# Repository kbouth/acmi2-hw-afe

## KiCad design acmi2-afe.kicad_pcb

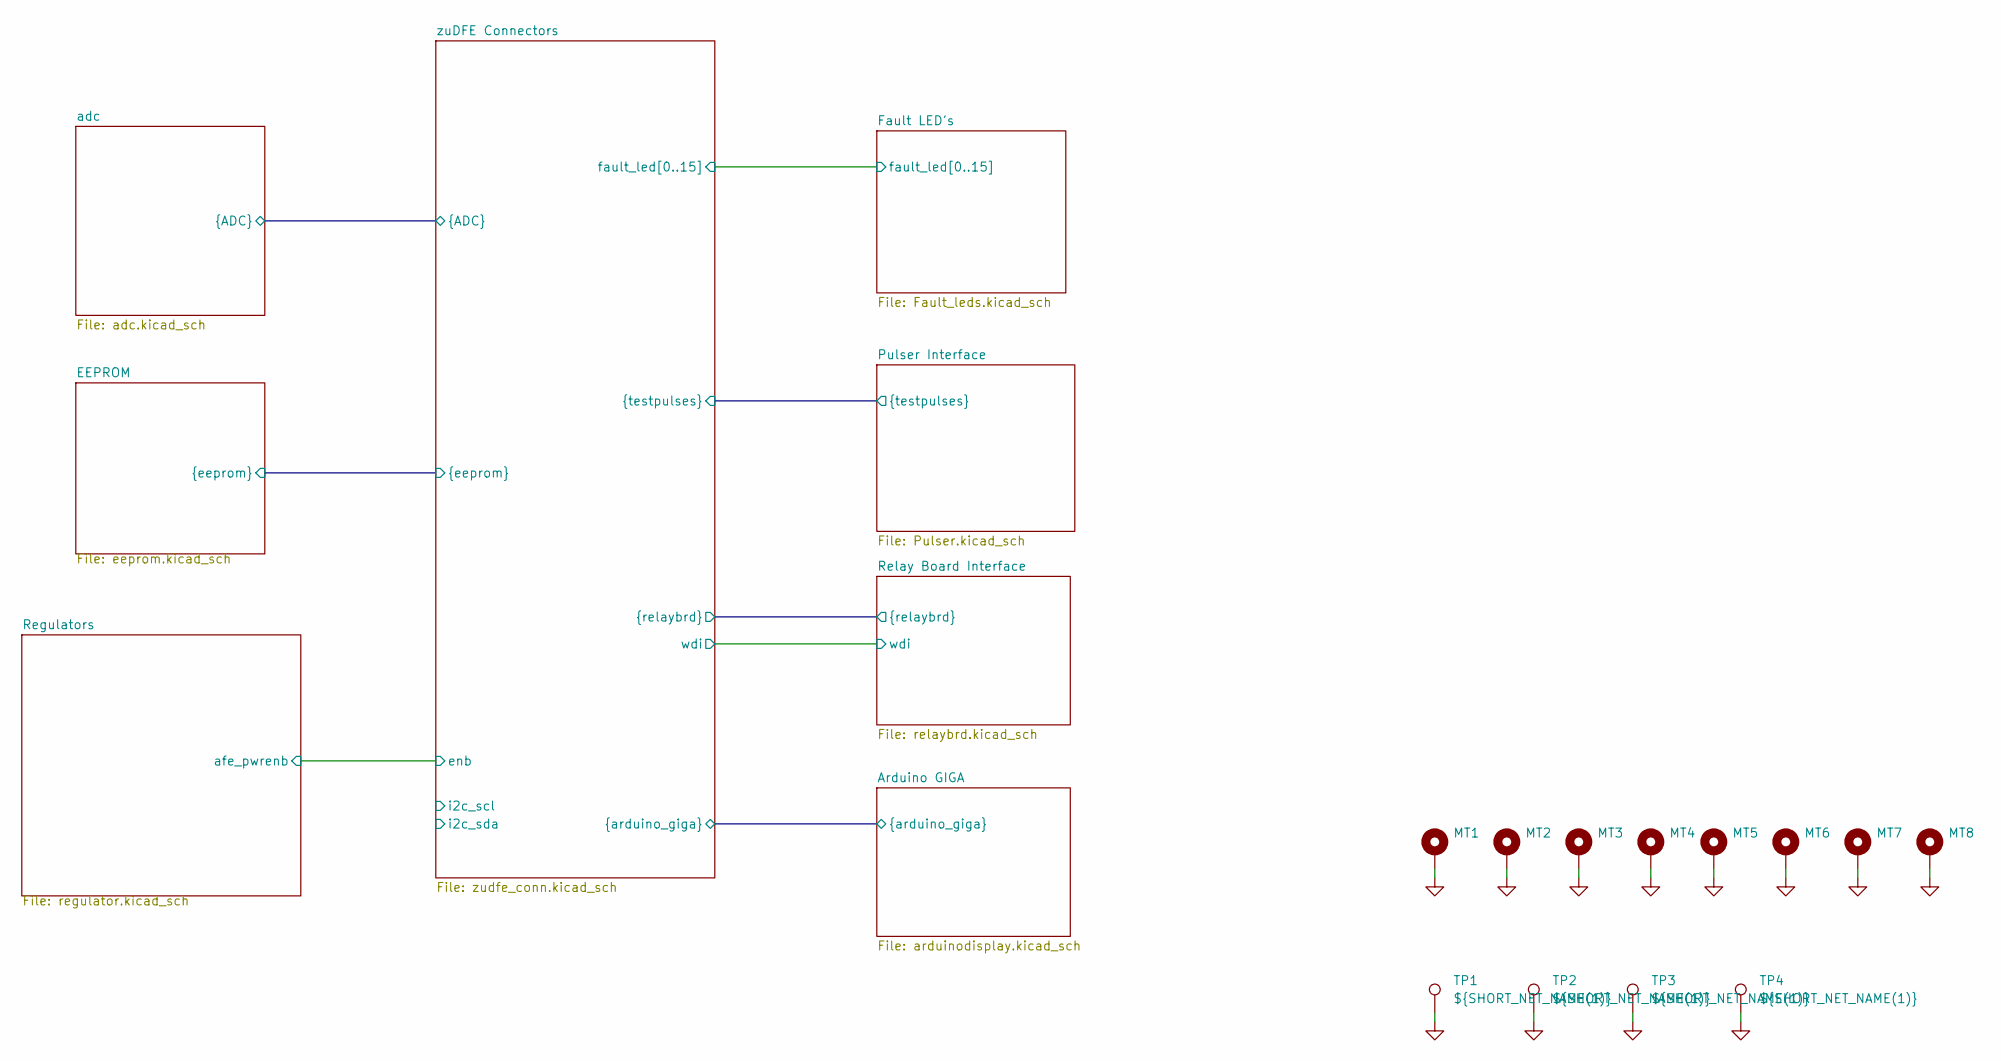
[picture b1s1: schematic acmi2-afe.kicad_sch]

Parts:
MT1, MT2, MT3, MT4, MT5, MT6, MT7, MT8: MountingHole_Pad; MountingHole_4.3mm_M4_DIN965_Pad
TP1, TP2, TP3, TP4: ${SHORT_NET_NAME(1)}; TestPoint_RCS-0C; MFG_PN RCS-0C

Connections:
GND: MT1.1 (1_1), MT2.1 (1_1), MT3.1 (1_1), MT4.1 (1_1), MT5.1 (1_1), MT6.1 (1_1), MT7.1 (1_1), MT8.1 (1_1), TP1.1 (1_1), TP2.1 (1_1), TP3.1 (1_1), TP4.1 (1_1); also elsewhere on the board

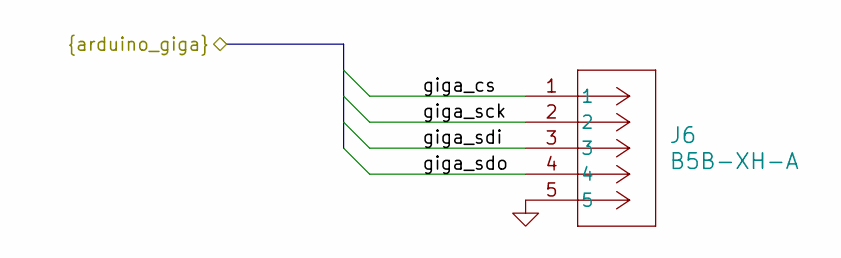
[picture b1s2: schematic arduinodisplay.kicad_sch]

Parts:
J6: B5B-XH-A; CONN_B5B-XH-A_JST

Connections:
/Arduino GIGA/giga_cs: J6.1; also elsewhere on the board
/Arduino GIGA/giga_sck: J6.2; also elsewhere on the board
/Arduino GIGA/giga_sdi: J6.3; also elsewhere on the board
/Arduino GIGA/giga_sdo: J6.4; also elsewhere on the board
GND: J6.5; also elsewhere on the board

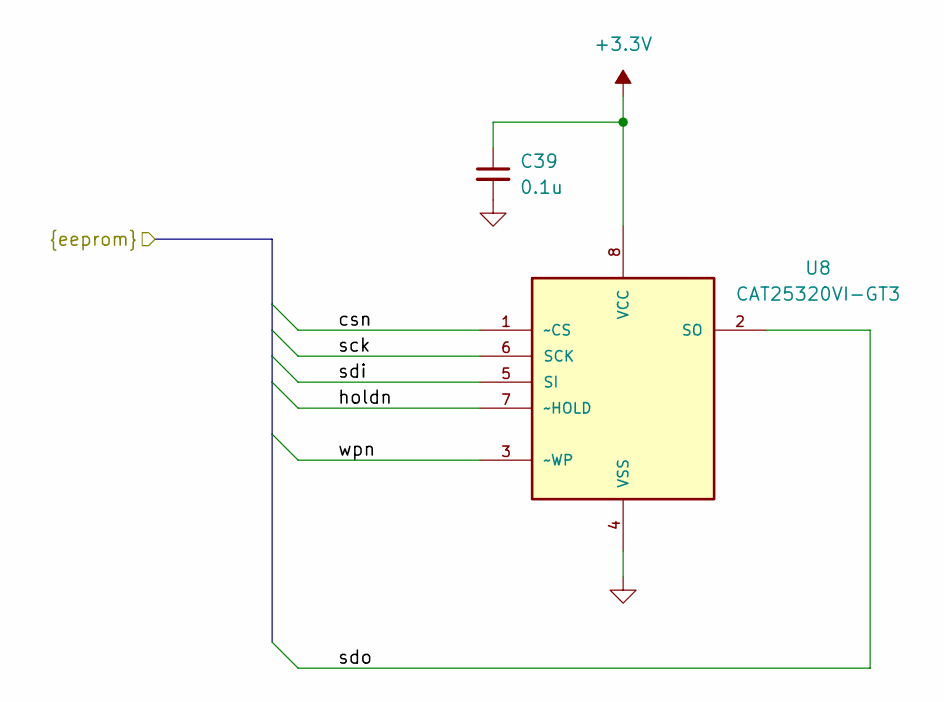
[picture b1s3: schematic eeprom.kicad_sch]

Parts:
C39: 0.1u; C_0805_2012Metric; MFG_PN TMF212B7104KGHT
U8: CAT25320VI-GT3; SOIC127P600X175-8N; MFG_PN CAT25320VI-GT3

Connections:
+3.3V: C39.1, U8.8 (VCC); also elsewhere on the board
/EEPROM/csn: U8.1 (~CS); also elsewhere on the board
/EEPROM/holdn: U8.7 (~HOLD); also elsewhere on the board
/EEPROM/sck: U8.6 (SCK); also elsewhere on the board
/EEPROM/sdi: U8.5 (SI); also elsewhere on the board
/EEPROM/sdo: U8.2 (SO); also elsewhere on the board
/EEPROM/wpn: U8.3 (~WP); also elsewhere on the board
GND: C39.2, U8.4 (VSS); also elsewhere on the board

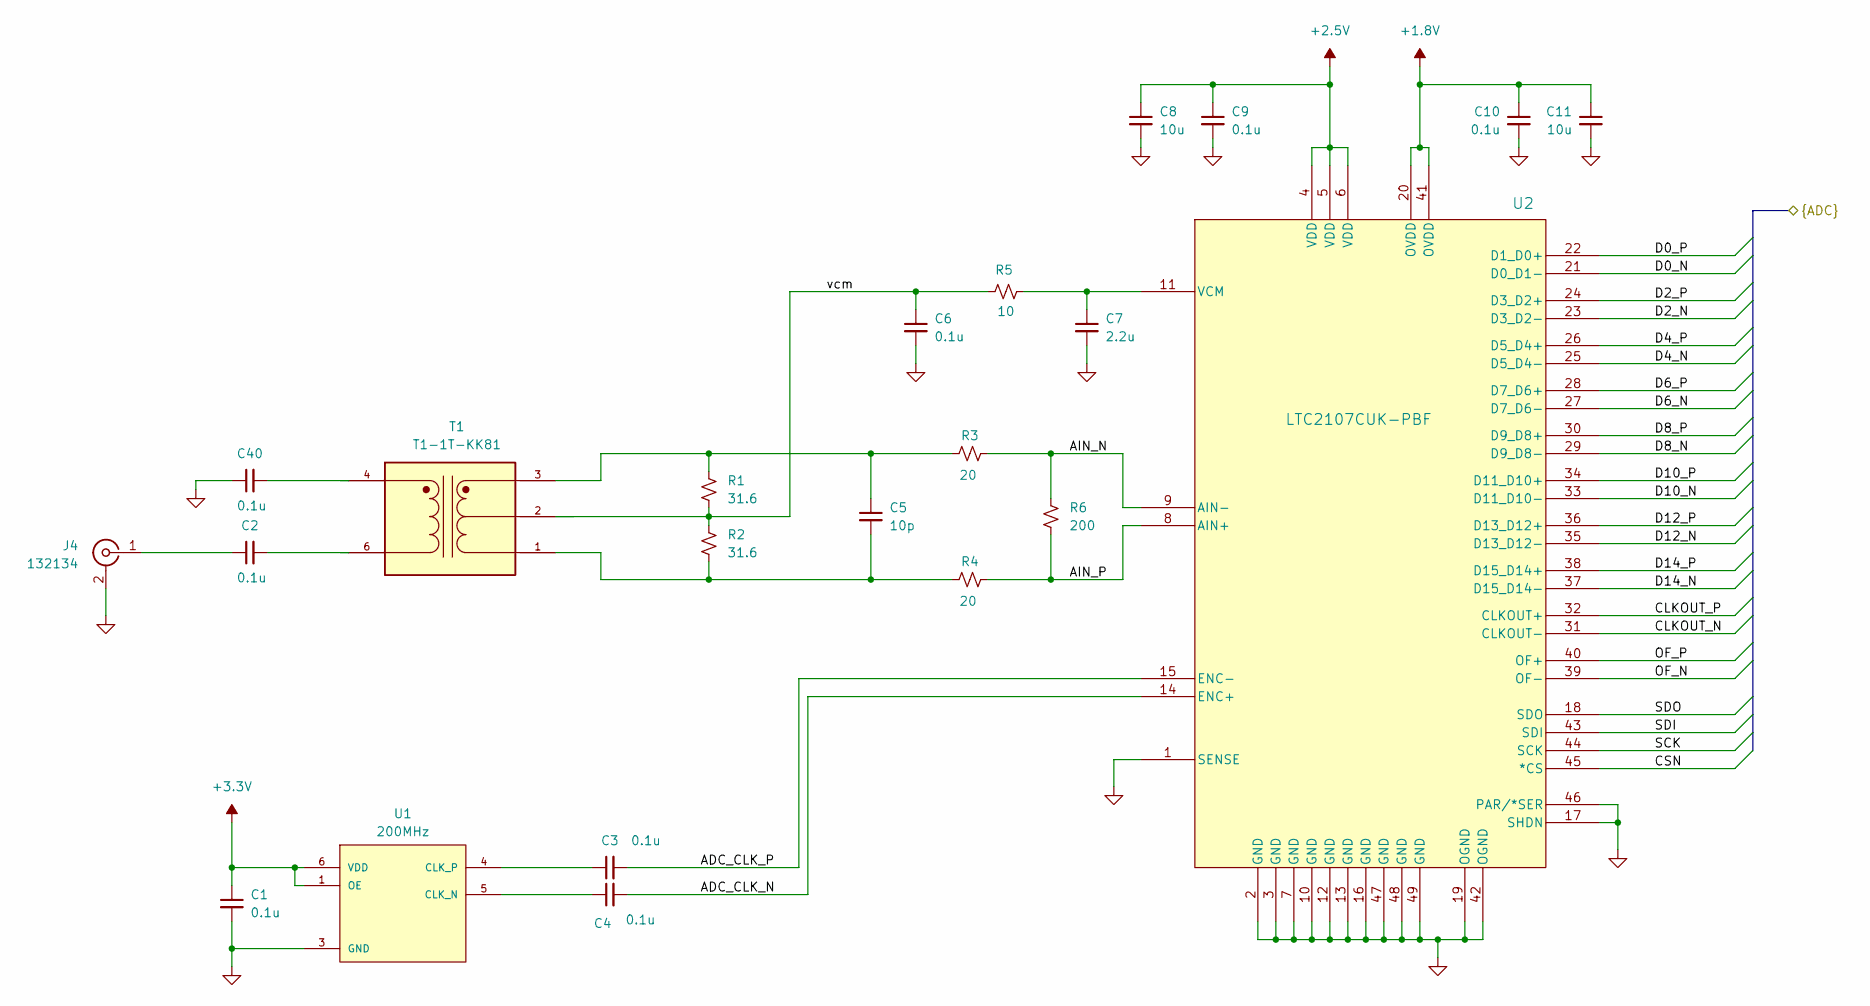
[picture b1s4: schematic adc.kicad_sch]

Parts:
C1, C2, C3, C4, C6, C9, C10, C40: 0.1u; C_0805_2012Metric; MFG_PN TMF212B7104KGHT
C5: 10p; C_0805_2012Metric; MFG_PN QVS212CG100JDHT
C7: 2.2u; C_0805_2012Metric; MFG_PN UMK212BB7225KG-T
C8, C11: 10u; C_0805_2012Metric; MFG_PN GRM21BR61C106KE15K
J4: 132134; SMA_Amphenol_132134_Vertical; MFG_PN 132134
R1, R2: 31.6; R_0805_2012Metric; MFG_PN ERJ-6ENF31R6V
R3, R4: 20; R_0805_2012Metric; MFG_PN ERJ-6ENF20R0V
R5: 10; R_0805_2012Metric; MFG_PN ERJ-6ENF10R0V
R6: 200; R_0805_2012Metric; MFG_PN ERJ-6ENF2000V
T1: T1-1T-KK81; XFMR_T1-1T-KK81_; PARTREV B
U1: 200MHz; OSC_ECS-LVDS33-2000-BN; MFG_PN ECS-LVDS33-2000-BN
U2: LTC2107CUK-PBF; QFN-48_UK_LIT; MFG_PN LTC2107CUK#PBF

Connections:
+1.8V: C10.1, C11.1, U2.20 (OVDD), U2.41 (OVDD); also elsewhere on the board
+2.5V: C8.1, C9.1, U2.4 (VDD), U2.5 (VDD), U2.6 (VDD); also elsewhere on the board
+3.3V: C1.1, U1.1 (OE), U1.6 (VDD); also elsewhere on the board
/adc/ADC_CLK_N: C4.2, U2.14 (ENC+)
/adc/ADC_CLK_P: C3.2, U2.15 (ENC-)
/adc/AIN_N: R3.1, R6.1, U2.9 (AIN-)
/adc/AIN_P: R4.1, R6.2, U2.8 (AIN+)
/adc/CLKOUT_N: U2.31 (CLKOUT-); also elsewhere on the board
/adc/CLKOUT_P: U2.32 (CLKOUT+); also elsewhere on the board
/adc/CSN: U2.45 (*CS); also elsewhere on the board
/adc/D0_N: U2.21 (D0_D1-); also elsewhere on the board
/adc/D0_P: U2.22 (D1_D0+); also elsewhere on the board
/adc/D2_N: U2.23 (D3_D2-); also elsewhere on the board
/adc/D2_P: U2.24 (D3_D2+); also elsewhere on the board
/adc/D4_N: U2.25 (D5_D4-); also elsewhere on the board
/adc/D4_P: U2.26 (D5_D4+); also elsewhere on the board
/adc/D6_N: U2.27 (D7_D6-); also elsewhere on the board
/adc/D6_P: U2.28 (D7_D6+); also elsewhere on the board
/adc/D8_N: U2.29 (D9_D8-); also elsewhere on the board
/adc/D8_P: U2.30 (D9_D8+); also elsewhere on the board
/adc/D10_N: U2.33 (D11_D10-); also elsewhere on the board
/adc/D10_P: U2.34 (D11_D10+); also elsewhere on the board
/adc/D12_N: U2.35 (D13_D12-); also elsewhere on the board
/adc/D12_P: U2.36 (D13_D12+); also elsewhere on the board
/adc/D14_N: U2.37 (D15_D14-); also elsewhere on the board
/adc/D14_P: U2.38 (D15_D14+); also elsewhere on the board
/adc/OF_N: U2.39 (OF-); also elsewhere on the board
/adc/OF_P: U2.40 (OF+); also elsewhere on the board
/adc/SCK: U2.44 (SCK); also elsewhere on the board
/adc/SDI: U2.43 (SDI); also elsewhere on the board
/adc/SDO: U2.18 (SDO); also elsewhere on the board
/adc/vcm: C6.1, R1.2, R2.1, R5.2, T1.2
GND: C1.2, C6.2, C7.2, C8.2, C9.2, C10.2, C11.2, C40.1, J4.2 (Ext), U1.3 (GND), U2.1 (SENSE), U2.2 (GND), U2.3 (GND), U2.7 (GND), U2.10 (GND), U2.12 (GND), U2.13 (GND), U2.16 (GND), U2.17 (SHDN), U2.19 (OGND), U2.42 (OGND), U2.46 (PAR/*SER), U2.47 (GND), U2.48 (GND), U2.49 (GND); also elsewhere on the board
unnamed: C2.2, T1.6
unnamed: C5.1, R1.1, R3.2, T1.3
unnamed: C5.2, R2.2, R4.2, T1.1
unnamed: C40.2, T1.4
unnamed: C2.1, J4.1 (In)
unnamed: C4.1, U1.5 (CLK_N)
unnamed: C3.1, U1.4 (CLK_P)
unnamed: C7.1, R5.1, U2.11 (VCM)

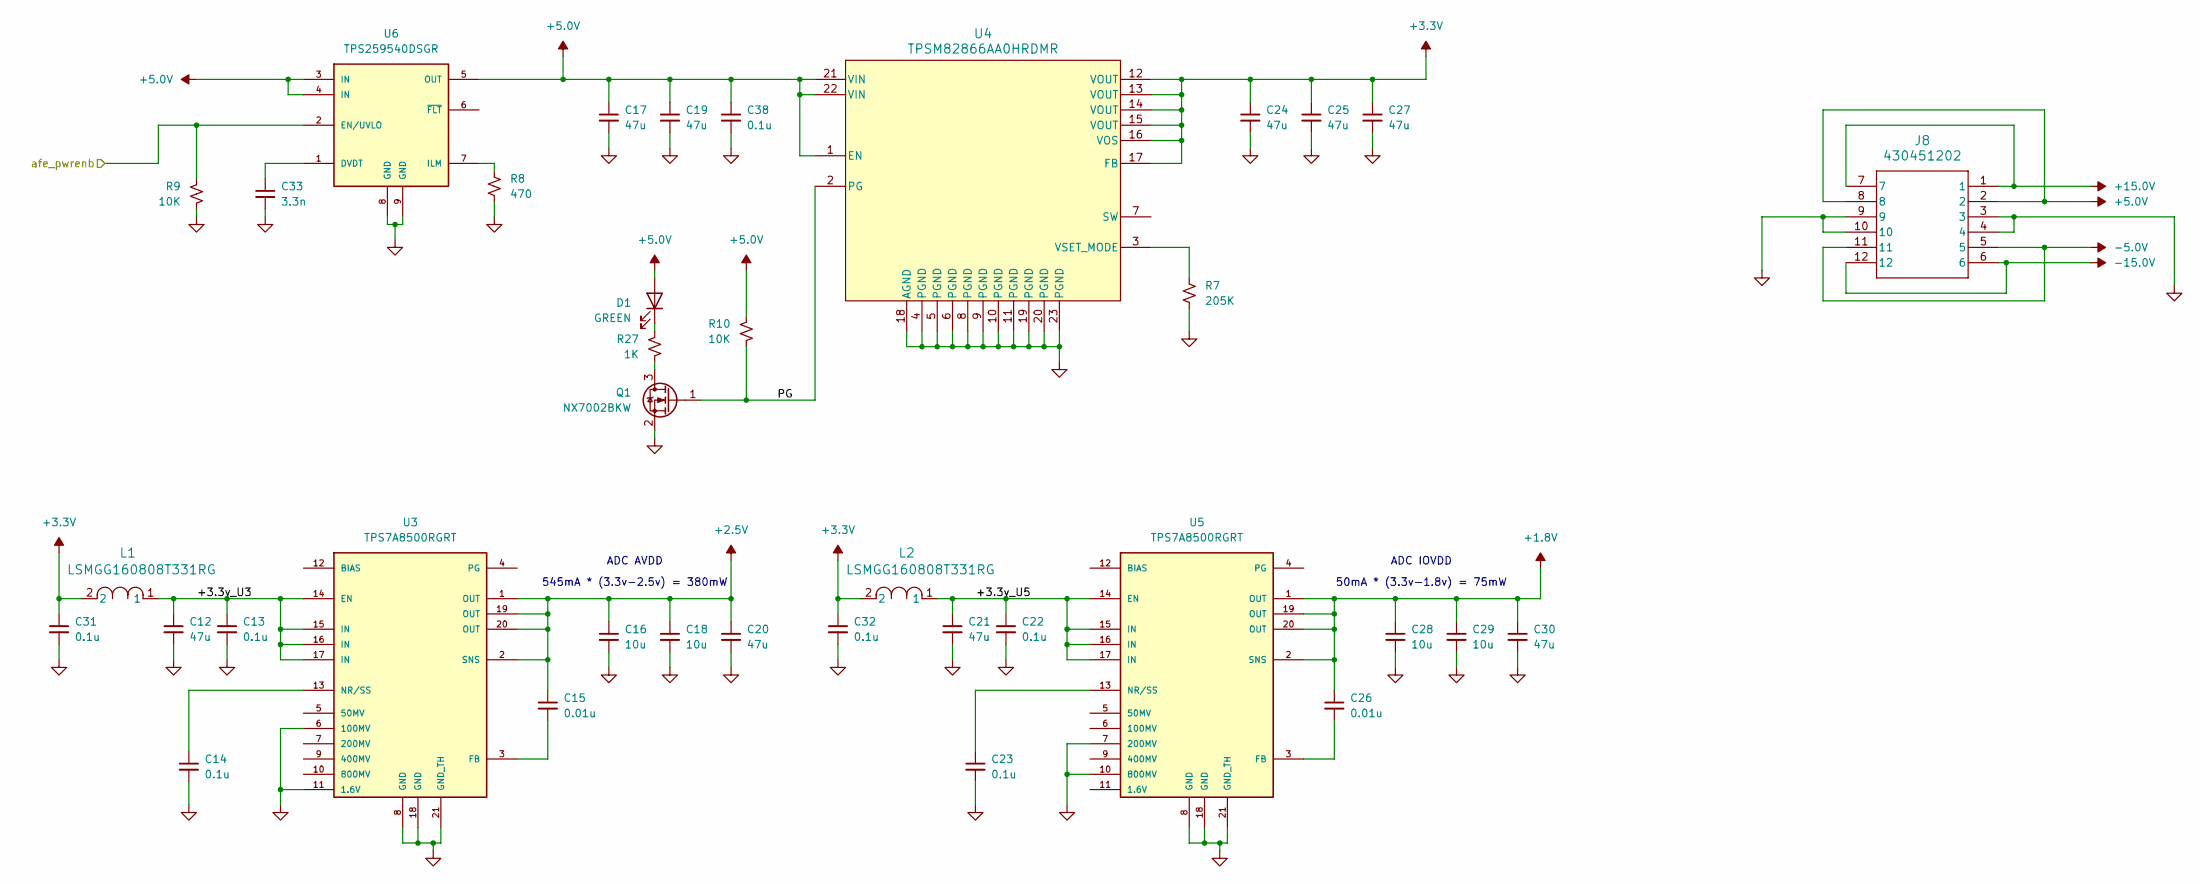
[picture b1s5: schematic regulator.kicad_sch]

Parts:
C12, C17, C19, C20, C21, C24, C25, C27, C30: 47u; C_0805_2012Metric; MFG_PN C2012X5R1A476M125AC
C13, C14, C22, C23, C31, C32, C38: 0.1u; C_0805_2012Metric; MFG_PN TMF212B7104KGHT
C15, C26: 0.01u; C_0805_2012Metric; MFG_PN MAASU21GSL8103MTNA01
C16, C18, C28, C29: 10u; C_0805_2012Metric; MFG_PN GRM21BR61C106KE15K
C33: 3.3n; C_0805_2012Metric; MFG_PN C0805X332K5RECTU
D1: GREEN; LED_0805_2012Metric; MFG_PN LTST-C191KGKT
J8: 430451202; CONN_SD-43045-001_12_MOL
L1, L2: LSMGG160808T331RG; IND_LSMG_160808_TAY; MFG_PN LSMGG160808T331RG
Q1: NX7002BKW; SOT-323_SC-70; MFG_PN NX7002BKWX
R7: 205K; R_0805_2012Metric; MFG_PN ERJ-6ENF2053V
R8: 470; R_0805_2012Metric; MFG_PN ERJ-6ENF4700V
R9, R10: 10K; R_0805_2012Metric; MFG_PN ERJ-2RKF1001X
R27: 1K; R_0805_2012Metric; MFG_PN ERJ-P06F1001V
U3, U5: TPS7A8500RGRT; QFN50P350X350X100-21N; MFG_PN TPS7A8500RGRT
U4: TPSM82866AA0HRDMR; RDM0023A-MFG; MFG_PN TPSM82866AA0HRDMR
U6: TPS259540DSGR; SON50P200X200X80-9N; MFG_PN TPS259540DSGR

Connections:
+1.8V: C26.1, C28.1, C29.1, C30.1, U5.1 (OUT), U5.2 (SNS), U5.19 (OUT), U5.20 (OUT); also elsewhere on the board
+2.5V: C15.1, C16.1, C18.1, C20.1, U3.1 (OUT), U3.2 (SNS), U3.19 (OUT), U3.20 (OUT); also elsewhere on the board
+3.3V: C24.1, C25.1, C27.1, C31.1, C32.1, L1.2, L2.2, U4.12 (VOUT), U4.13 (VOUT), U4.14 (VOUT), U4.15 (VOUT), U4.16 (VOS), U4.17 (FB); also elsewhere on the board
+5.0V: C17.1, C19.1, C38.1, D1.2 (A), J8.2, J8.8, R10.1, U4.1 (EN), U4.21 (VIN), U4.22 (VIN), U6.3 (IN), U6.4 (IN), U6.5 (OUT); also elsewhere on the board
+15.0V: J8.1, J8.7; also elsewhere on the board
-5.0V: J8.5, J8.11; also elsewhere on the board
-15.0V: J8.6, J8.12; also elsewhere on the board
/Regulators/+3.3v_U3: C12.1, C13.1, L1.1, U3.14 (EN), U3.15 (IN), U3.16 (IN), U3.17 (IN)
/Regulators/+3.3v_U5: C21.1, C22.1, L2.1, U5.14 (EN), U5.15 (IN), U5.16 (IN), U5.17 (IN)
/Regulators/PG: Q1.1 (G), R10.2, U4.2 (PG)
/Regulators/afe_pwrenb: R9.1, U6.2 (EN/UVLO); also elsewhere on the board
GND: C12.2, C13.2, C14.2, C16.2, C17.2, C18.2, C19.2, C20.2, C21.2, C22.2, C23.2, C24.2, C25.2, C27.2, C28.2, C29.2, C30.2, C31.2, C32.2, C33.2, C38.2, J8.3, J8.4, J8.9, J8.10, Q1.2 (S), R7.2, R8.2, R9.2, U3.6 (100MV), U3.8 (GND), U3.11 (1.6V), U3.18 (GND), U3.21 (GND_TH), U4.4 (PGND), U4.5 (PGND), U4.6 (PGND), U4.8 (PGND), U4.9 (PGND), U4.10 (PGND), U4.11 (PGND), U4.18 (AGND), U4.19 (PGND), U4.20 (PGND), U4.23 (PGND), U5.7 (200MV), U5.8 (GND), U5.10 (800MV), U5.18 (GND), U5.21 (GND_TH), U6.8 (GND), U6.9 (GND); also elsewhere on the board
unnamed: D1.1 (K), R27.1
unnamed: Q1.3 (D), R27.2
unnamed: C15.2, U3.3 (FB)
unnamed: C14.1, U3.13 (NR/SS)
unnamed: R7.1, U4.3 (VSET_MODE)
unnamed: C26.2, U5.3 (FB)
unnamed: C23.1, U5.13 (NR/SS)
unnamed: C33.1, U6.1 (DVDT)
unnamed: R8.1, U6.7 (ILM)

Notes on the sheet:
50mA * (3.3v-1.8v) = 75mW
ADC IOVDD
ADC AVDD
545mA * (3.3v-2.5v) = 380mW

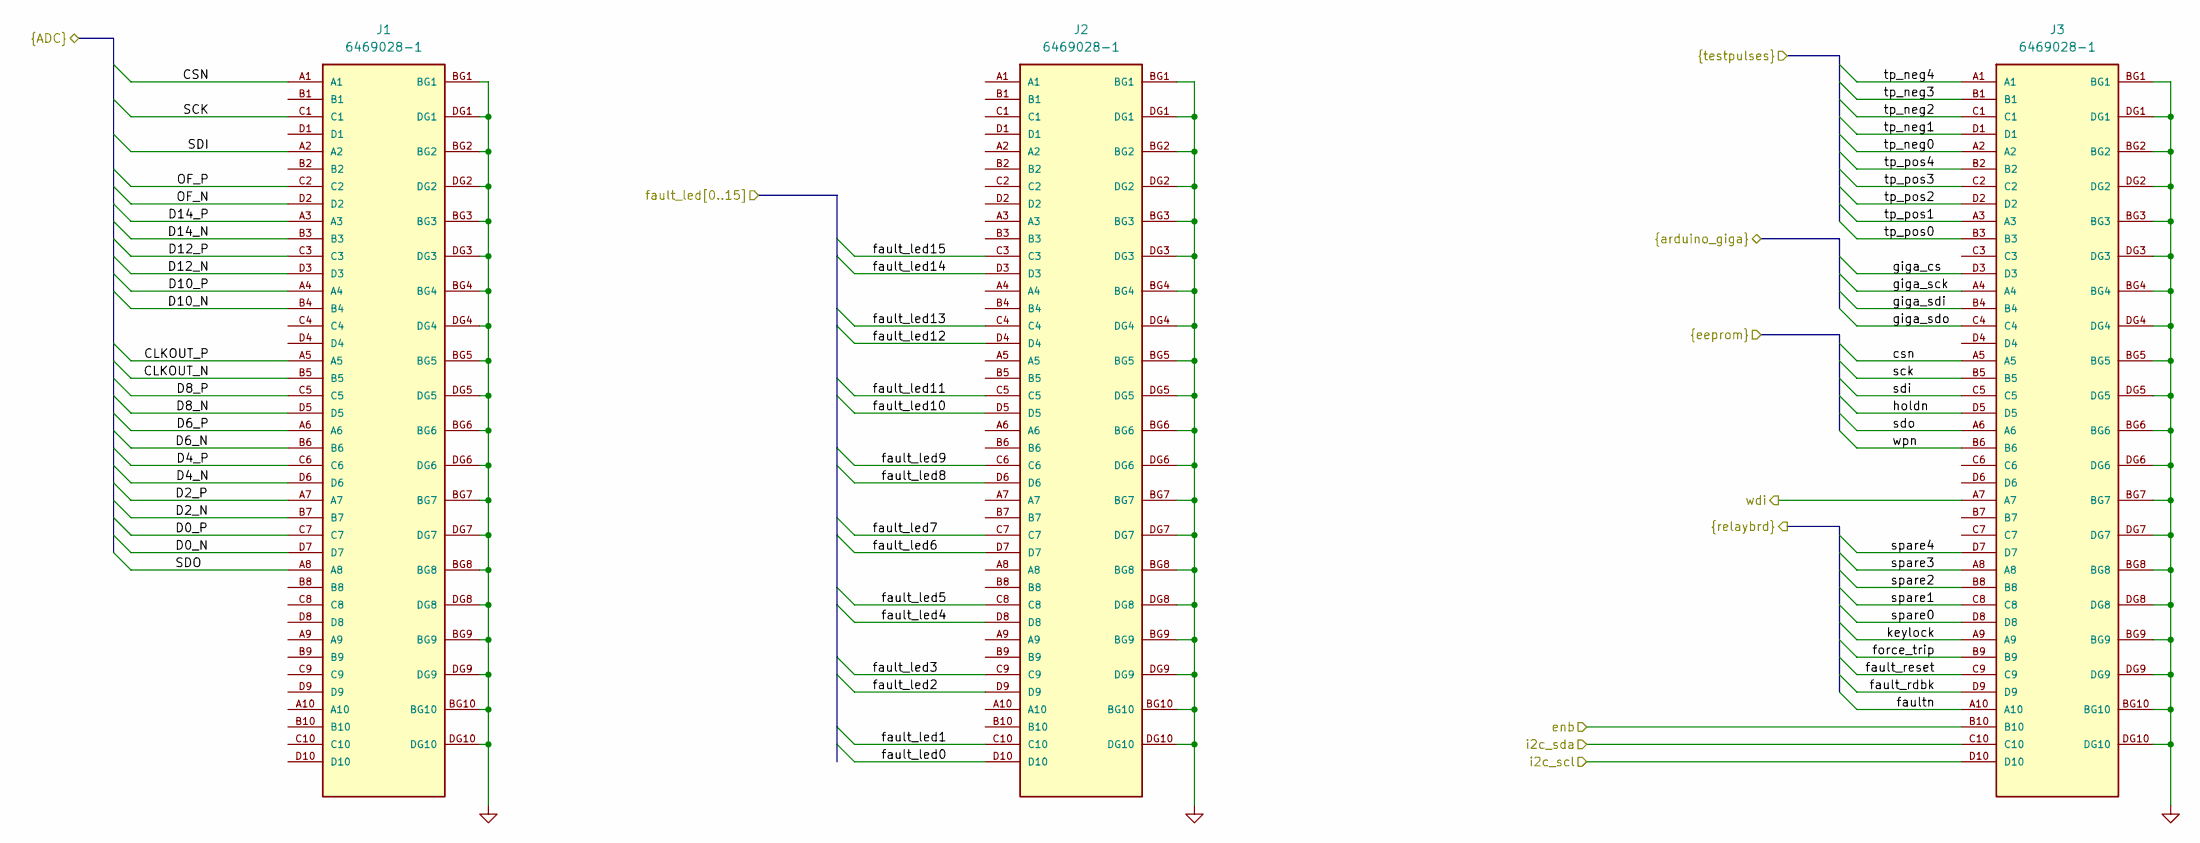
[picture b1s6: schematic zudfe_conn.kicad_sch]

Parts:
J1, J2, J3: 6469028-1; TE_6469028-1; PARTREV E

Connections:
/Arduino GIGA/giga_cs: J3.D3; also elsewhere on the board
/Arduino GIGA/giga_sck: J3.A4; also elsewhere on the board
/Arduino GIGA/giga_sdi: J3.B4; also elsewhere on the board
/Arduino GIGA/giga_sdo: J3.C4; also elsewhere on the board
/EEPROM/csn: J3.A5; also elsewhere on the board
/EEPROM/holdn: J3.D5; also elsewhere on the board
/EEPROM/sck: J3.B5; also elsewhere on the board
/EEPROM/sdi: J3.C5; also elsewhere on the board
/EEPROM/sdo: J3.A6; also elsewhere on the board
/EEPROM/wpn: J3.B6; also elsewhere on the board
/Fault LED's/fault_led0: J2.D10; also elsewhere on the board
/Fault LED's/fault_led1: J2.C10; also elsewhere on the board
/Fault LED's/fault_led2: J2.D9; also elsewhere on the board
/Fault LED's/fault_led3: J2.C9; also elsewhere on the board
/Fault LED's/fault_led4: J2.D8; also elsewhere on the board
/Fault LED's/fault_led5: J2.C8; also elsewhere on the board
/Fault LED's/fault_led6: J2.D7; also elsewhere on the board
/Fault LED's/fault_led7: J2.C7; also elsewhere on the board
/Fault LED's/fault_led8: J2.D6; also elsewhere on the board
/Fault LED's/fault_led9: J2.C6; also elsewhere on the board
/Fault LED's/fault_led10: J2.D5; also elsewhere on the board
/Fault LED's/fault_led11: J2.C5; also elsewhere on the board
/Fault LED's/fault_led12: J2.D4; also elsewhere on the board
/Fault LED's/fault_led13: J2.C4; also elsewhere on the board
/Fault LED's/fault_led14: J2.D3; also elsewhere on the board
/Fault LED's/fault_led15: J2.C3; also elsewhere on the board
/Pulser Interface/tp_neg0: J3.A2; also elsewhere on the board
/Pulser Interface/tp_neg1: J3.D1; also elsewhere on the board
/Pulser Interface/tp_neg2: J3.C1; also elsewhere on the board
/Pulser Interface/tp_neg3: J3.B1; also elsewhere on the board
/Pulser Interface/tp_neg4: J3.A1; also elsewhere on the board
/Pulser Interface/tp_pos0: J3.B3; also elsewhere on the board
/Pulser Interface/tp_pos1: J3.A3; also elsewhere on the board
/Pulser Interface/tp_pos2: J3.D2; also elsewhere on the board
/Pulser Interface/tp_pos3: J3.C2; also elsewhere on the board
/Pulser Interface/tp_pos4: J3.B2; also elsewhere on the board
/Regulators/afe_pwrenb: J3.B10; also elsewhere on the board
/Relay Board Interface/fault_rdbk: J3.D9; also elsewhere on the board
/Relay Board Interface/fault_reset: J3.C9; also elsewhere on the board
/Relay Board Interface/faultn: J3.A10; also elsewhere on the board
/Relay Board Interface/force_trip: J3.B9; also elsewhere on the board
/Relay Board Interface/keylock: J3.A9; also elsewhere on the board
/Relay Board Interface/spare0: J3.D8; also elsewhere on the board
/Relay Board Interface/spare1: J3.C8; also elsewhere on the board
/Relay Board Interface/spare2: J3.B8; also elsewhere on the board
/Relay Board Interface/spare3: J3.A8; also elsewhere on the board
/Relay Board Interface/spare4: J3.D7; also elsewhere on the board
/Relay Board Interface/wdi: J3.A7; also elsewhere on the board
/adc/CLKOUT_N: J1.B5; also elsewhere on the board
/adc/CLKOUT_P: J1.A5; also elsewhere on the board
/adc/CSN: J1.A1; also elsewhere on the board
/adc/D0_N: J1.D7; also elsewhere on the board
/adc/D0_P: J1.C7; also elsewhere on the board
/adc/D2_N: J1.B7; also elsewhere on the board
/adc/D2_P: J1.A7; also elsewhere on the board
/adc/D4_N: J1.D6; also elsewhere on the board
/adc/D4_P: J1.C6; also elsewhere on the board
/adc/D6_N: J1.B6; also elsewhere on the board
/adc/D6_P: J1.A6; also elsewhere on the board
/adc/D8_N: J1.D5; also elsewhere on the board
/adc/D8_P: J1.C5; also elsewhere on the board
/adc/D10_N: J1.B4; also elsewhere on the board
/adc/D10_P: J1.A4; also elsewhere on the board
/adc/D12_N: J1.D3; also elsewhere on the board
/adc/D12_P: J1.C3; also elsewhere on the board
/adc/D14_N: J1.B3; also elsewhere on the board
/adc/D14_P: J1.A3; also elsewhere on the board
/adc/OF_N: J1.D2; also elsewhere on the board
/adc/OF_P: J1.C2; also elsewhere on the board
/adc/SCK: J1.C1; also elsewhere on the board
/adc/SDI: J1.A2; also elsewhere on the board
/adc/SDO: J1.A8; also elsewhere on the board
/zuDFE Connectors/i2c_scl: J3.D10
/zuDFE Connectors/i2c_sda: J3.C10
GND: J1.BG1, J1.BG2, J1.BG3, J1.BG4, J1.BG5, J1.BG6, J1.BG7, J1.BG8, J1.BG9, J1.BG10, J1.DG1, J1.DG2, J1.DG3, J1.DG4, J1.DG5, J1.DG6, J1.DG7, J1.DG8, J1.DG9, J1.DG10, J2.BG1, J2.BG2, J2.BG3, J2.BG4, J2.BG5, J2.BG6, J2.BG7, J2.BG8, J2.BG9, J2.BG10, J2.DG1, J2.DG2, J2.DG3, J2.DG4, J2.DG5, J2.DG6, J2.DG7, J2.DG8, J2.DG9, J2.DG10, J3.BG1, J3.BG2, J3.BG3, J3.BG4, J3.BG5, J3.BG6, J3.BG7, J3.BG8, J3.BG9, J3.BG10, J3.DG1, J3.DG2, J3.DG3, J3.DG4, J3.DG5, J3.DG6, J3.DG7, J3.DG8, J3.DG9, J3.DG10; also elsewhere on the board

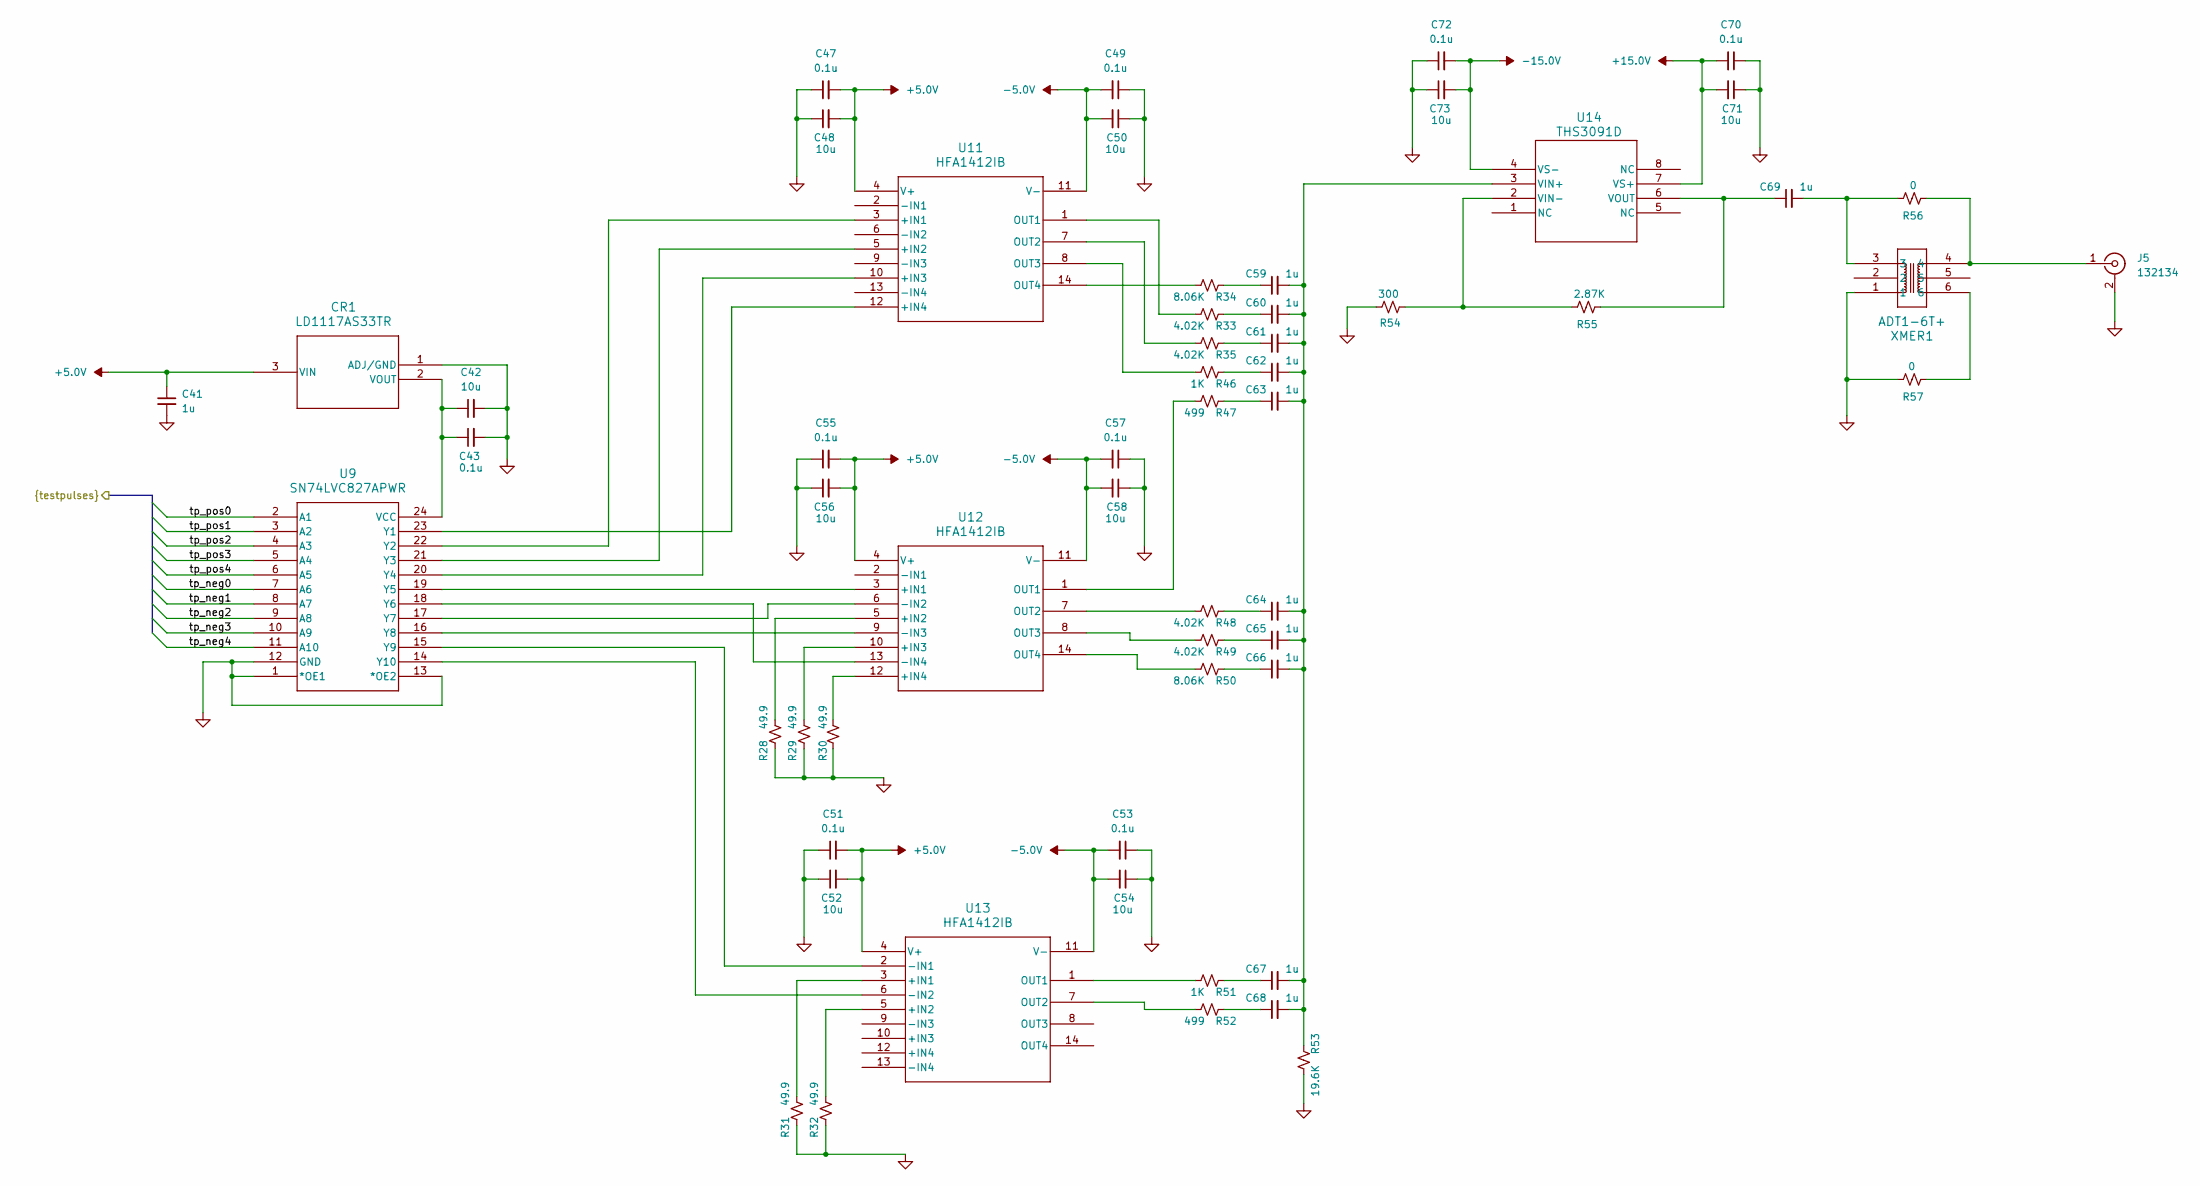
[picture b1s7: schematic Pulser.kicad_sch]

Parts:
C41, C59, C60, C61, C62, C63, C64, C65, C66, C67, C68, C69: 1u; C_0805_2012Metric; MFG_PN TMF212B7104KGHT
C42: 10u; C_0805_2012Metric; MFG_PN TMF212B7104KGHT
C43: 0.1u; C_1206_3216Metric; MFG_PN TMF212B7104KGHT
C47, C49, C51, C53, C55, C57, C70, C72: 0.1u; C_0805_2012Metric; MFG_PN TMF212B7104KGHT
C48, C50, C52, C54, C56, C58, C71, C73: 10u; C_1206_3216Metric; MFG_PN TMF212B7104KGHT
CR1: LD1117AS33TR; SOT-223_STM
J5: 132134; SMA_Amphenol_132134_Vertical; MFG_PN 132134
R28, R29, R30, R31, R32: 49.9; R_0805_2012Metric; MFG_PN ERJ-6ENF31R6V
R33, R35, R48, R49: 4.02K; R_0805_2012Metric; MFG_PN ERJ-6ENF31R6V
R34, R50: 8.06K; R_0805_2012Metric; MFG_PN ERJ-6ENF31R6V
R46, R51: 1K; R_0805_2012Metric; MFG_PN ERJ-6ENF31R6V
R47, R52: 499; R_0805_2012Metric; MFG_PN ERJ-6ENF31R6V
R53: 19.6K; R_0805_2012Metric; MFG_PN ERJ-6ENF31R6V
R54: 300; R_0805_2012Metric; MFG_PN ERJ-6ENF31R6V
R55: 2.87K; R_0805_2012Metric; MFG_PN ERJ-6ENF31R6V
R56, R57: 0; R_0805_2012Metric; MFG_PN ERJ-6ENF31R6V
U9: SN74LVC827APWR; PW24
U11, U12, U13: HFA1412IB; SOIC14_4X8P75_INR
U14: THS3091D; D8
XMER1: ADT1-6T+; CD637_MNC

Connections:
+5.0V: C41.1, C47.2, C48.2, C51.2, C52.2, C55.2, C56.2, CR1.3 (VIN), U11.4 (V+), U12.4 (V+), U13.4 (V+); also elsewhere on the board
+15.0V: C70.2, C71.2, U14.7 (VS+); also elsewhere on the board
-5.0V: C49.2, C50.2, C53.2, C54.2, C57.2, C58.2, U11.11 (V-), U12.11 (V-), U13.11 (V-); also elsewhere on the board
-15.0V: C72.2, C73.2, U14.4 (VS-); also elsewhere on the board
/Pulser Interface/tp_neg0: U9.7 (A6); also elsewhere on the board
/Pulser Interface/tp_neg1: U9.8 (A7); also elsewhere on the board
/Pulser Interface/tp_neg2: U9.9 (A8); also elsewhere on the board
/Pulser Interface/tp_neg3: U9.10 (A9); also elsewhere on the board
/Pulser Interface/tp_neg4: U9.11 (A10); also elsewhere on the board
/Pulser Interface/tp_pos0: U9.2 (A1); also elsewhere on the board
/Pulser Interface/tp_pos1: U9.3 (A2); also elsewhere on the board
/Pulser Interface/tp_pos2: U9.4 (A3); also elsewhere on the board
/Pulser Interface/tp_pos3: U9.5 (A4); also elsewhere on the board
/Pulser Interface/tp_pos4: U9.6 (A5); also elsewhere on the board
GND: C41.2, C42.2, C43.2, C47.1, C48.1, C49.1, C50.1, C51.1, C52.1, C53.1, C54.1, C55.1, C56.1, C57.1, C58.1, C70.1, C71.1, C72.1, C73.1, CR1.1 (ADJ/GND), J5.2 (Ext), R28.2, R29.2, R30.2, R31.2, R32.2, R53.1, R54.2, R57.2, U9.1 (*OE1), U9.12 (GND), U9.13 (*OE2), XMER1.1; also elsewhere on the board
unnamed: C59.1, R34.2
unnamed: C60.1, R33.2
unnamed: C61.1, R35.2
unnamed: C62.1, R46.2
unnamed: C63.1, R47.2
unnamed: C64.1, R48.2
unnamed: C65.1, R49.2
unnamed: C66.1, R50.2
unnamed: C67.1, R51.2
unnamed: C68.1, R52.2
unnamed: C69.2, R56.2, XMER1.3
unnamed: C42.1, C43.1, CR1.2 (VOUT), U9.24 (VCC)
unnamed: J5.1 (In), R56.1, XMER1.4
unnamed: R57.1, XMER1.6
unnamed: U9.22 (Y2), U11.3 (+IN1)
unnamed: U9.21 (Y3), U11.5 (+IN2)
unnamed: U9.20 (Y4), U11.10 (+IN3)
unnamed: U9.23 (Y1), U11.12 (+IN4)
unnamed: R33.1, U11.1 (OUT1)
unnamed: R35.1, U11.7 (OUT2)
unnamed: R46.1, U11.8 (OUT3)
unnamed: R34.1, U11.14 (OUT4)
unnamed: U9.19 (Y5), U12.3 (+IN1)
unnamed: R28.1, U12.5 (+IN2)
unnamed: R29.1, U12.10 (+IN3)
unnamed: R30.1, U12.12 (+IN4)
unnamed: U9.17 (Y7), U12.6 (-IN2)
unnamed: U9.16 (Y8), U12.9 (-IN3)
unnamed: U9.18 (Y6), U12.13 (-IN4)
unnamed: R47.1, U12.1 (OUT1)
unnamed: R48.1, U12.7 (OUT2)
unnamed: R49.1, U12.8 (OUT3)
unnamed: R50.1, U12.14 (OUT4)
unnamed: R31.1, U13.3 (+IN1)
unnamed: R32.1, U13.5 (+IN2)
unnamed: U9.15 (Y9), U13.2 (-IN1)
unnamed: U9.14 (Y10), U13.6 (-IN2)
unnamed: R51.1, U13.1 (OUT1)
unnamed: R52.1, U13.7 (OUT2)
unnamed: C59.2, C60.2, C61.2, C62.2, C63.2, C64.2, C65.2, C66.2, C67.2, C68.2, R53.2, U14.3 (VIN+)
unnamed: R54.1, R55.2, U14.2 (VIN-)
unnamed: C69.1, R55.1, U14.6 (VOUT)
